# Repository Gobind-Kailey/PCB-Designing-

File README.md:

# PCB-Designing
My first PCB design project, created to learn the basics of PCB layout, schematic capture, and manufacturing.

This project is my first attempt at designing a printed circuit board (PCB).  
The goal was to better understand how PCBs are made, starting from schematic capture in KiCad and moving into PCB layout and manufacturing preparation.

---

## 📌 Project Overview
- **Tool Used**: KiCad 
- **Board Type**: 2-layer
- **Purpose**: Practice learning PCB design workflow
- **Features**:  
  - Basic schematic capture
  - Component placement and routing
  
---

## 🖼️ PCB Preview

PCB Schematic Images: (Finished Design) 

STM32CubeIDE 1.18.1:

PCB Editor: (Finished Design)

PCB Board 

---

## 📂 Repository Contents
- `/schematics` – circuit schematic files  
- `/pcb` – board layout files  
- `/images` – renders/screenshots of the PCB  

---

## 🚀 Lessons Learned
- Learned schematic capture in KiCad
- Understood how to translate schematics into PCB layout
- Used Design Rule Checker (DRC) for debugging
- Practiced efficient routing and grounding

---

## 🔮 Next Steps
- Send this design to be manufactured  
- Test soldering and assembly  
- Improve the design with revisions  

---

## 📖 License
This project is open-source and shared for learning purposes.

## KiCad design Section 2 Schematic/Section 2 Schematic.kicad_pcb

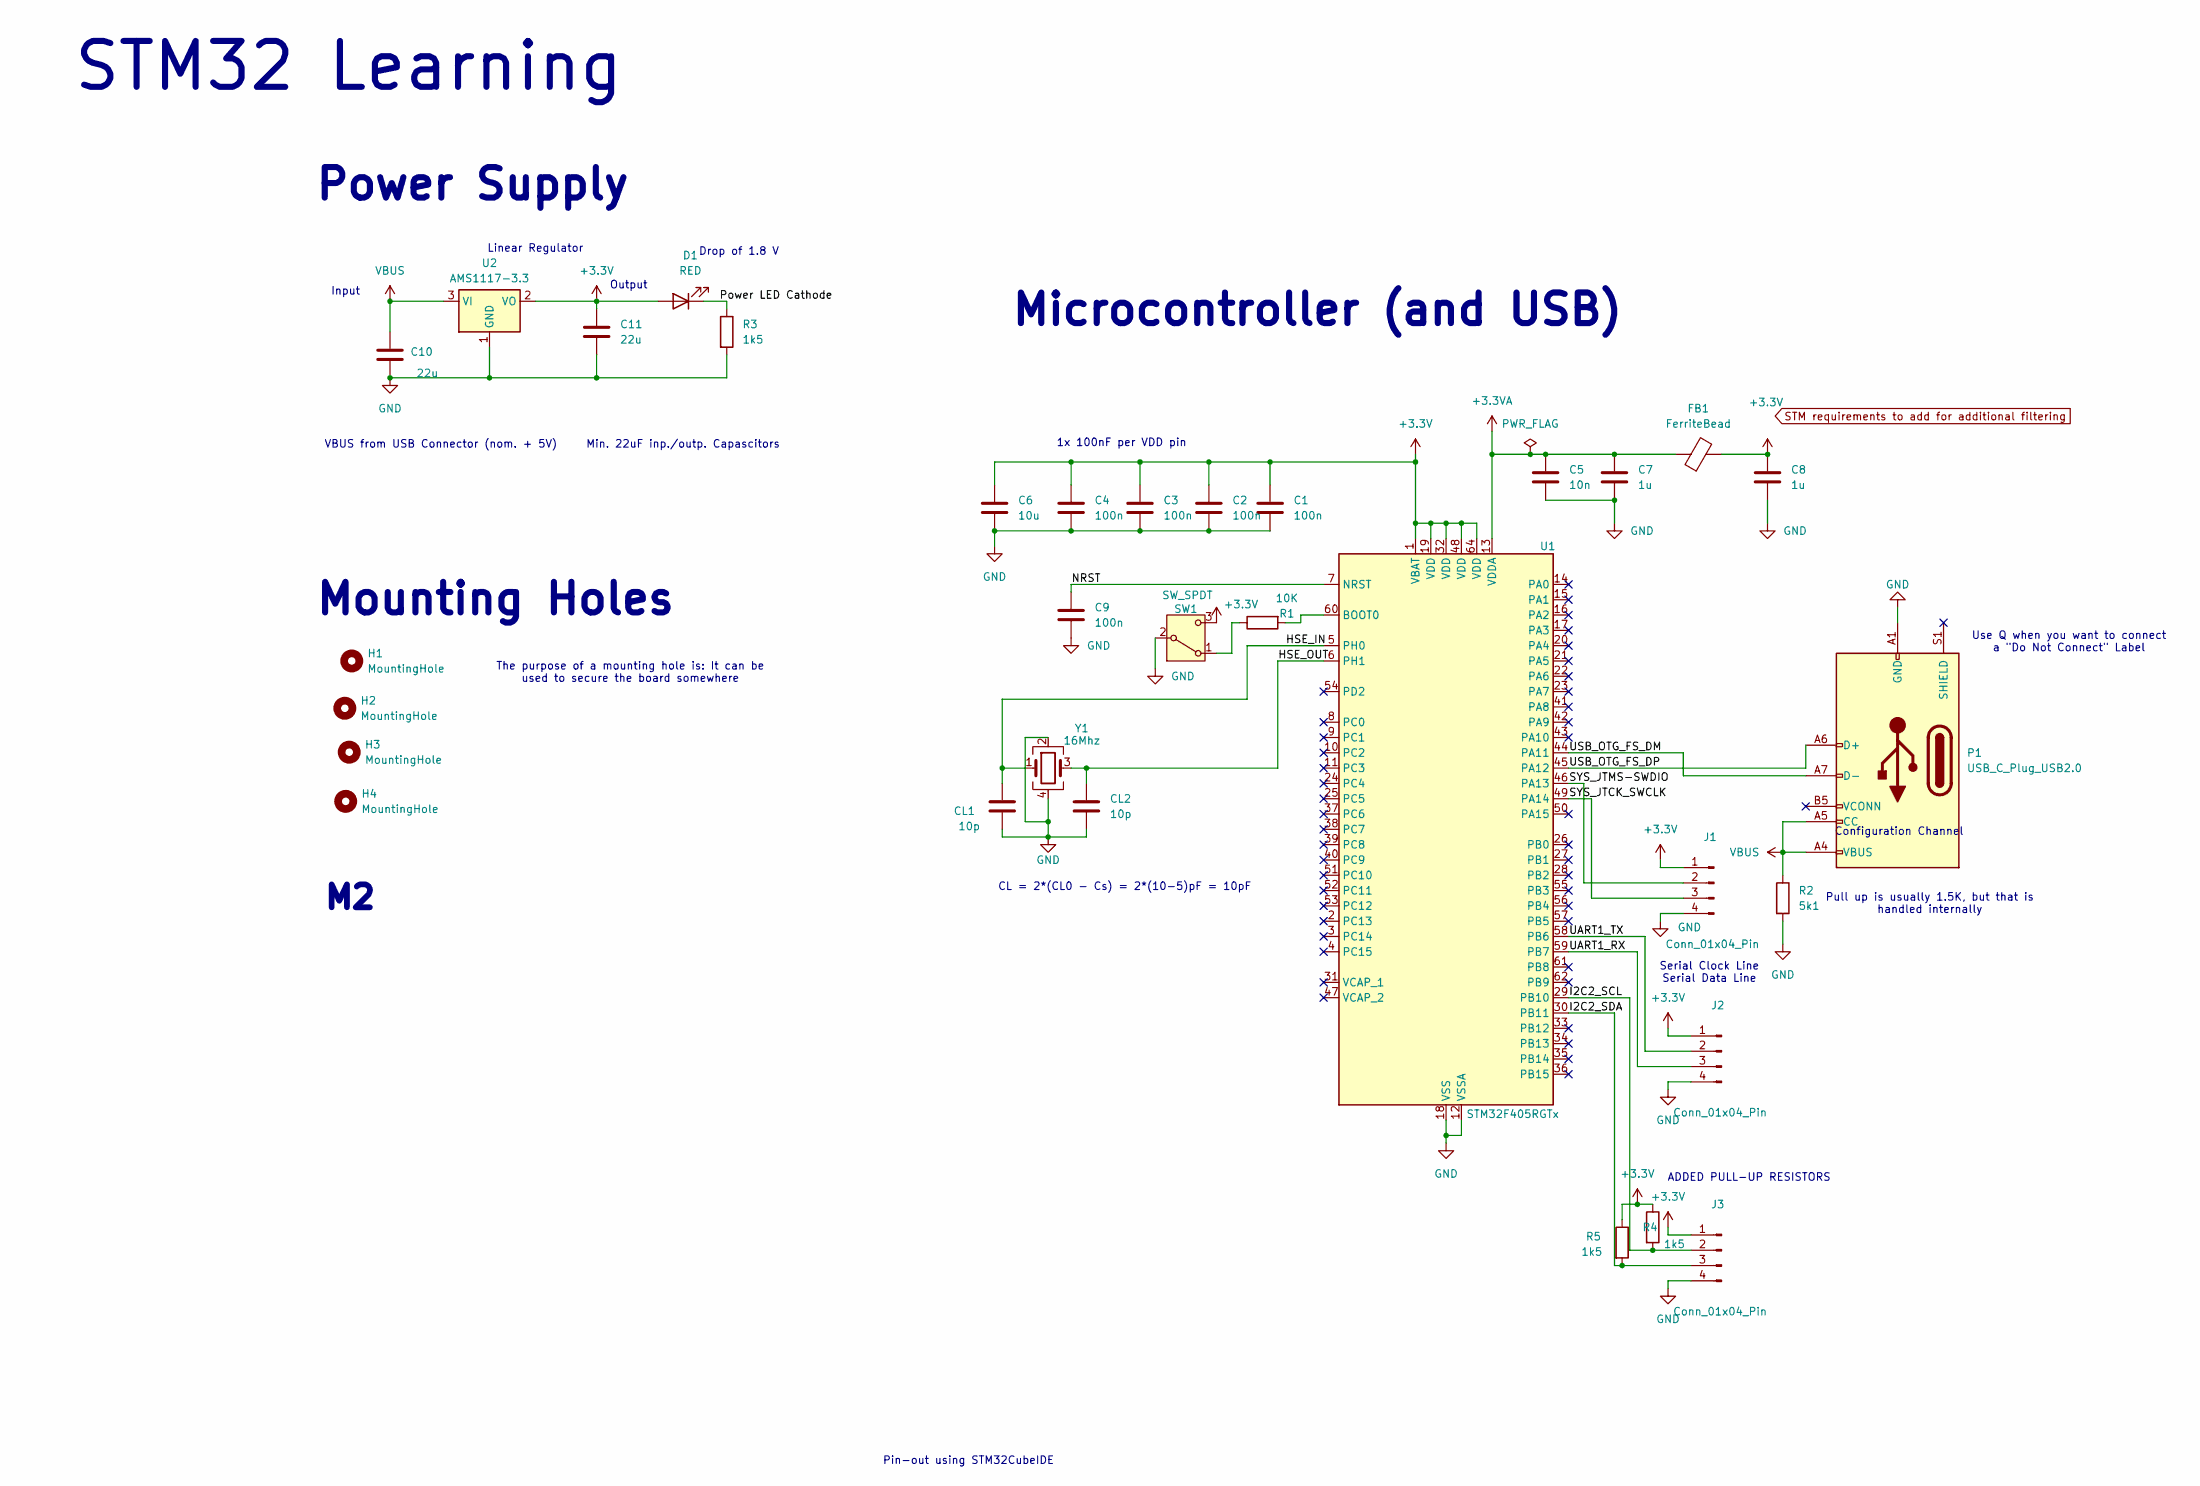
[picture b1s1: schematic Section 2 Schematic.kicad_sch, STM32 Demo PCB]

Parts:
C1, C2, C3, C4, C9: 100n; C_0402_1005Metric
C5: 10n; C_0402_1005Metric
C6: 10u; C_0603_1608Metric
C7, C8: 1u; C_0402_1005Metric
C10, C11: 22u; C_0805_2012Metric
CL1, CL2: 10p; C_0402_1005Metric
D1: RED; LED_0603_1608Metric
FB1: FerriteBead; L_0603_1608Metric
H1, H2, H3, H4: MountingHole; MountingHole_2.2mm_M2
J1, J2, J3: Conn_01x04_Pin; PinHeader_1x04_P2.54mm_Vertical
P1: USB_C_Plug_USB2.0; USB_C_Plug_JAE_DX07P024AJ1
R1: 10K; R_0402_1005Metric
R2: 5k1; R_0402_1005Metric
R3, R4, R5: 1k5; R_0402_1005Metric
SW1: SW_SPDT; SW_SPDT_PCM12
U1: STM32F405RGTx; LQFP-64_10x10mm_P0.5mm
U2: AMS1117-3.3; SOT-223-3_TabPin2
Y1: 16Mhz; Crystal_SMD_3225-4Pin_3.2x2.5mm

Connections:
+3.3V: C1.1, C2.1, C3.1, C4.1, C6.1, C8.1, C11.1, D1.2 (A), FB1.2, J1.1, J2.1, J3.1, R4.1, R5.1, SW1.3 (C), U1.1 (VBAT), U1.19 (VDD), U1.32 (VDD), U1.48 (VDD), U1.64 (VDD), U2.2 (VO)
+3.3VA: C5.1, C7.1, FB1.1, U1.13 (VDDA)
/HSE_IN: CL1.1, U1.5 (PH0), Y1.1
/HSE_OUT: CL2.1, U1.6 (PH1), Y1.3
/I2C2_SCL: J3.2, R4.2, U1.29 (PB10)
/I2C2_SDA: J3.3, R5.2, U1.30 (PB11)
/NRST: C9.1, U1.7 (NRST)
/Power LED Cathode: D1.1 (K), R3.1
/SYS_JTCK_SWCLK: J1.3, U1.49 (PA14)
/SYS_JTMS-SWDIO: J1.2, U1.46 (PA13)
/UART1_RX: J2.3, U1.59 (PB7)
/UART1_TX: J2.2, U1.58 (PB6)
/USB_OTG_FS_DM: P1.A7 (D-), U1.44 (PA11)
/USB_OTG_FS_DP: P1.A6 (D+), U1.45 (PA12)
GND: C1.2, C2.2, C3.2, C4.2, C5.2, C6.2, C7.2, C8.2, C9.2, C10.2, C11.2, CL1.2, CL2.2, J1.4, J2.4, J3.4, P1.A1 (GND), P1.A12 (GND), P1.B1 (GND), P1.B12 (GND), R2.2, R3.2, SW1.2 (B), U1.12 (VSSA), U1.18 (VSS), U1.63 (VSS), U2.1 (GND), Y1.2, Y1.4
unnamed: R1.1, SW1.1 (A)
unnamed: R1.2, U1.60 (BOOT0)
VBUS: C10.1, P1.A4 (VBUS), P1.A5 (CC), P1.A9 (VBUS), P1.B4 (VBUS), P1.B9 (VBUS), R2.1, U2.3 (VI)

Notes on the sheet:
Pull up is usually 1.5K, but that is handled internally
1x 100nF per VDD pin
STM32 Learning
Linear Regulator
CL = 2*(CL0 - Cs) = 2*(10-5)pF = 10pF
Use Q when you want to connect a "Do Not Connect" Label
Configuration Channel
Power Supply
Microcontroller (and USB)
Output
The purpose of a mounting hole is: It can be used to secure the board somewhere
Serial Clock Line Serial Data Line
Drop of 1.8 V
VBUS from USB Connector (nom. + 5V) Min. 22uF inp./outp. Capascitors
Input
Pin-out using STM32CubeIDE
ADDED PULL-UP RESISTORS
Mounting Holes

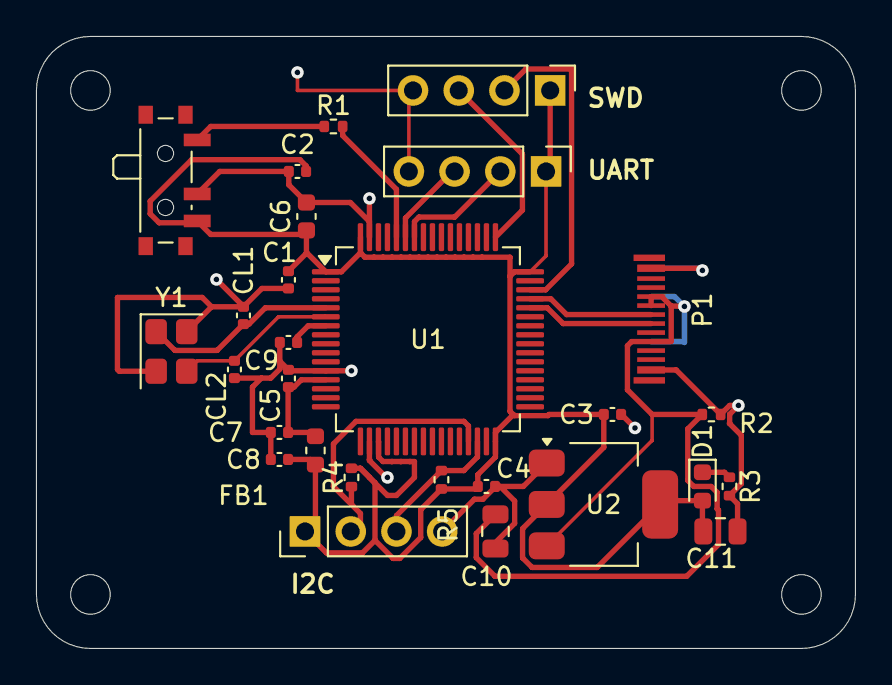
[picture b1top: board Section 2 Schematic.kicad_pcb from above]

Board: 2 copper layers, 45.5 x 34.0 mm, 32 parts (0 on the bottom side), 18 nets.

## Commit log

2025-08-31 Uploading all the files for this PCB Project
